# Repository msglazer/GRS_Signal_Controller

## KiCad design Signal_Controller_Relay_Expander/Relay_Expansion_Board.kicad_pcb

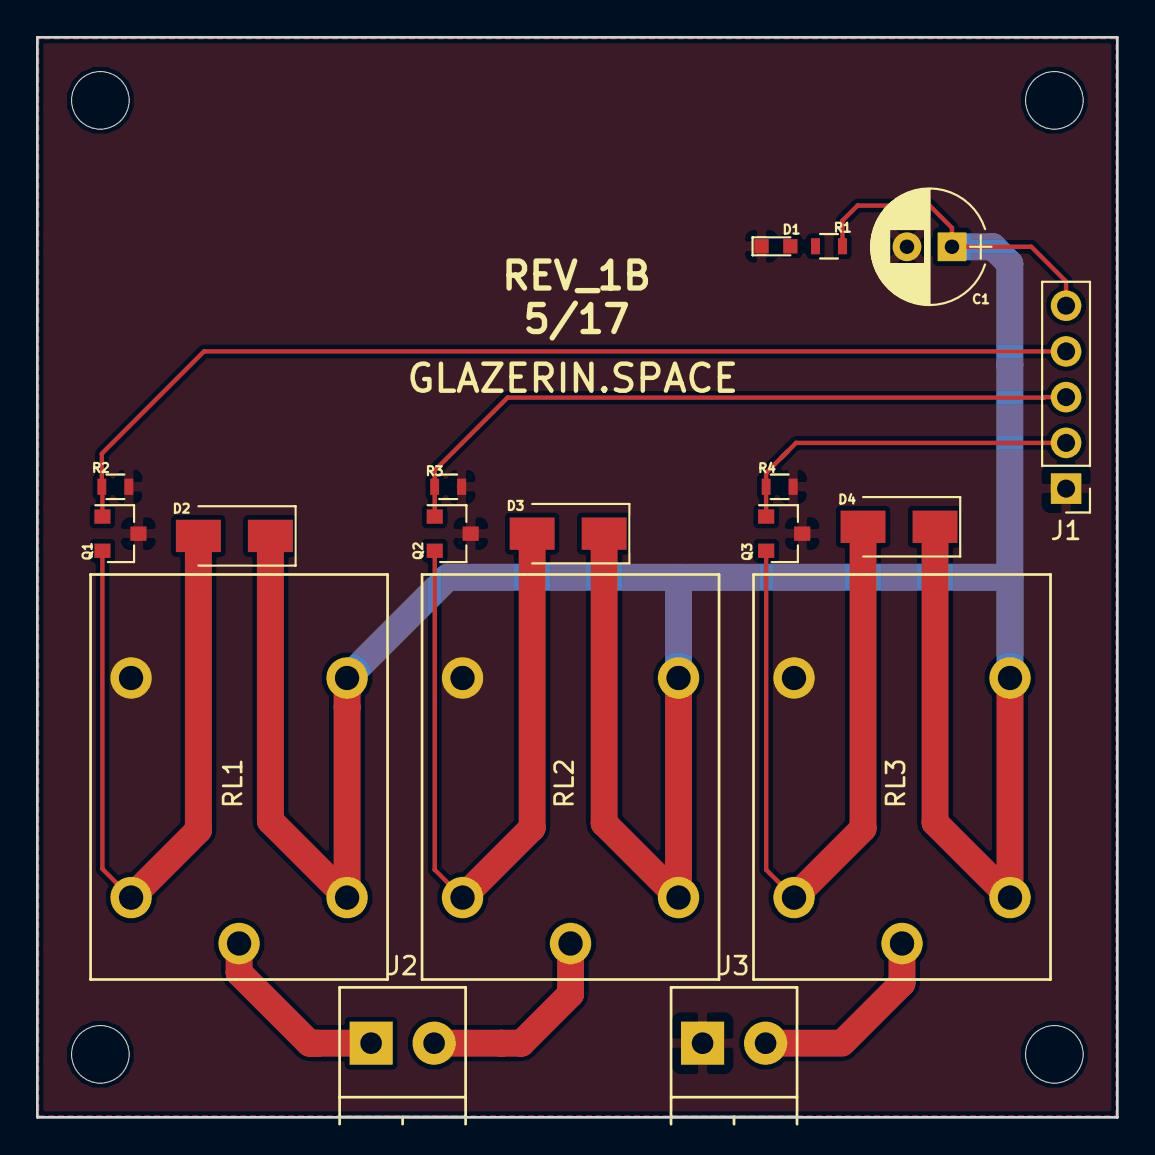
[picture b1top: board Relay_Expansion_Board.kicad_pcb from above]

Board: 2 copper layers, 60.0 x 60.0 mm, 18 parts (0 on the bottom side), 12 nets.

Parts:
C1: 100uF; CP_Radial_D6.3mm_P2.50mm
D1: LED; LED_0603
D2, D3, D4: FM5819-W; D_SMA_Standard
J1: CONN_01X05; Pin_Header_Straight_1x05_Pitch2.54mm
J2, J3: CONN_01X02; TerminalBlock_Pheonix_PT-3.5mm_2pol
Q1, Q2, Q3: 2N7002P,215; SOT-23
R1: R; R_0603
R2, R3, R4: 10K; R_0603
RL1, RL2, RL3: G5LE-1; G5LE-14-DC12

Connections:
+12V: C1.1, D2.1, D3.1, D4.1, J1.5, R1.1, RL1.2, RL1.3, RL2.2, RL2.3, RL3.2, RL3.3
/BULB_2: J3.2, RL3.1
/COIL_2A: J2.1, RL1.1
/COIL_2B: J2.2, RL2.1
/RELAY_4: J1.4, Q1.1, R2.1
/RELAY_5: J1.3, Q2.1, R3.1
/RELAY_6: J1.2, Q3.1, R4.1
GND: C1.2, D1.1, J1.1, J3.1, Q1.3, Q2.3, Q3.3, R2.2, R3.2, R4.2, RL1.4, RL2.4, RL3.4
unnamed: D1.2, R1.2
unnamed: D2.2, Q1.2, RL1.5
unnamed: D3.2, Q2.2, RL2.5
unnamed: D4.2, Q3.2, RL3.5

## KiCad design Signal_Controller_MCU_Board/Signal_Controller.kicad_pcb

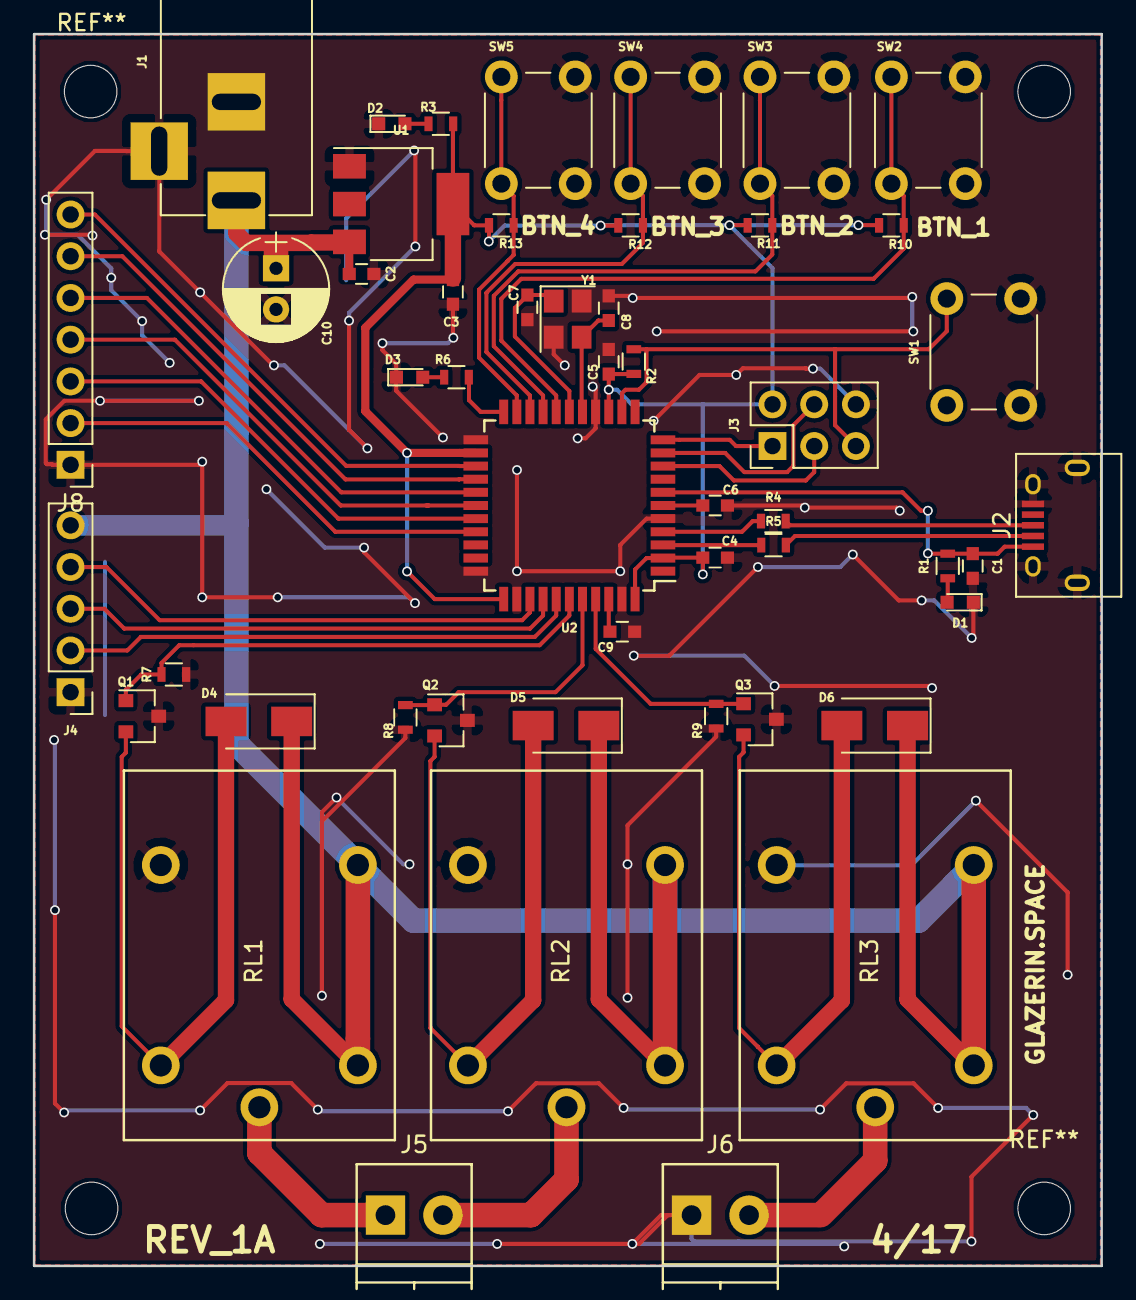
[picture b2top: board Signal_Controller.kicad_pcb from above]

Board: 2 copper layers, 65.0 x 75.0 mm, 50 parts (0 on the bottom side), 42 nets.

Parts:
C1, C2, C3, C4, C5, C6, C9: 1uF; C_0603
C7, C8: 22pF; C_0603
C10: CP1; CP_Radial_D6.3mm_P2.50mm
D1, D2, D3: LED; LED_0603
D4, D5, D6: FM5819-W; D_SMA_Standard
J1: BARREL_JACK
J2: USB_OTG; USB_Micro-B
J3: CONN_02X03; Pin_Header_Straight_2x03_Pitch2.54mm
J4: CONN_01X03; Pin_Header_Straight_1x05_Pitch2.54mm
J5, J6: CONN_01X02; TerminalBlock_Pheonix_PT-3.5mm_2pol
J8: CONN_01X07; Pin_Header_Straight_1x07_Pitch2.54mm
Q1, Q2, Q3: 2N7002P,215; SOT-23
R1, R3, R6: 1K; R_0603
R2, R7, R8, R9, R10, R11, R12, R13: 10K; R_0603
R4, R5: 22; R_0603
RL1, RL2, RL3: G5LE-1; G5LE-14-DC12
SW1, SW2, SW3, SW4, SW5: SW_Push; SW_PUSH_6mm_h13mm
U1: AZ1117IH-5.0TRG1; SOT-223
U2: ATmega32U4; TQFP-44_10x10mm_Pitch0.8mm
Y1: Crystal; Crystal_SMD_3225-4pin_3.2x2.5mm

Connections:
+5V: C3.1, C4.1, C5.1, J3.2, R2.1, R3.1, R10.1, R11.1, R12.1, R13.1, U1.2, U2.2, U2.14, U2.24, U2.34, U2.44
+12V: C2.1, C10.1, D4.1, D5.1, D6.1, J1.1, J4.5, RL1.2, RL1.3, RL2.2, RL2.3, RL3.2, RL3.3, U1.3
/BULB_1: J6.2, RL3.1
/BUTTON_1: R10.2, SW2.1, U2.18
/BUTTON_2: R11.2, SW3.1, U2.19
/BUTTON_3: R12.2, SW4.1, U2.25
/BUTTON_4: R13.2, SW5.1, U2.26
/COIL_1A: J5.1, RL1.1
/COIL_1B: J5.2, RL2.1
/D+: J2.3, R4.2
/D-: J2.2, R5.2
/GPIO_1: J8.5, U2.27
/GPIO_2: J8.4, U2.28
/GPIO_3: J8.3, U2.29
/GPIO_4: J8.2, U2.30
/MISO: J3.1, U2.11
/MOSI: J3.4, U2.10
/RELAY_1: Q1.1, R7.1, U2.39
/RELAY_2: Q2.1, R8.1, U2.40
/RELAY_3: Q3.1, R9.1, U2.41
/RELAY_4: J4.4, U2.36
/RELAY_5: J4.3, U2.37
/RELAY_6: J4.2, U2.38
/RST: J3.5, R2.2, SW1.1, U2.13
/RXI: J8.7, U2.20
/SCK: J3.3, U2.9
/TXO: J8.6, U2.21
/V_BUS: C1.1, J2.1, R1.2, U2.7
GND: C1.2, C2.2, C3.2, C4.2, C5.2, C6.2, C7.1, C8.1, C9.2, C10.2, D1.1, D2.1, D3.1, J1.2, J1.3, J2.5, J2.6, J3.6, J4.1, J6.1, J8.1, Q1.3, Q2.3, Q3.3, R7.2, R8.2, R9.2, RL1.4, RL2.4, RL3.4, SW1.2, SW2.2, SW3.2, SW4.2, SW5.2, U1.1, U2.5, U2.15, U2.23, U2.33, U2.35, U2.43, Y1.2, Y1.4
unnamed: C6.1, U2.6
unnamed: C7.2, U2.17, Y1.1
unnamed: C8.2, U2.16, Y1.3
unnamed: C9.1, U2.42
unnamed: D1.2, R1.1
unnamed: D2.2, R3.2
unnamed: D3.2, R6.1
unnamed: D4.2, Q1.2, RL1.5
unnamed: D5.2, Q2.2, RL2.5
unnamed: D6.2, Q3.2, RL3.5
unnamed: R4.1, U2.4
unnamed: R5.1, U2.3
unnamed: R6.2, U2.22

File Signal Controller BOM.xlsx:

Bill of Materials (BOM) - Wearable Main PCB
> All parts seperated by color, GREEN for Main board, BLUE for Expansion board
Item # | Qty | Ref Des | Manufacturer | Mfg Part # | Dist. Part # | Price Per Unit | Total Price | Description | Package | Type | Datasheet |  |  |  |  |  | Notes
1 | 1 | U1 | Diodes Inc. | AZ1117IH-5.0TRG1 | 621-AZ1117IH-5.0TRG1 | 0.4 | 0.4 | 5V Regulator | SOT-223 | SMD | http://www.mouser.com/ds/2/115/AZ1117-776390.pdf
2 | 1 | U2 | Atmel | ATMEGA32U4RC-AU | 556-ATMEGA32U4RC-AU | 4.09 | 4.09 | Atmega32u4 MCU | TQFP-44 | SMD | http://www.mouser.com/ds/2/268/Atmel-7766-8-bit-AVR-ATmega16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
4 | 7 | C1,C2,C3,C4,C5,C6,C9 | Murata Electronics | GRM188R61E105KA12J | 81-GRM188R61E105KA2J | 0.1 | 0.70000000000000007 | 1uF Capacitor | 0603 | SMD | http://www.mouser.com/ds/2/281/c02e-2905.pdf
5 | 2 | C7,C8 | Vishay / Vitramon | VJ0603A220JXACW1BC | 77-VJ0603A220JXACBC | 0.06 | 0.12 | 22pF Capacitor | 0603 | SMD | http://www.mouser.com/ds/2/427/vjw1bcbascomseries-223529.pdf
7 | 1 | C10 | Lelon | RGA101M1EBK-0611G | 140-RGA101M1EBK0611G | 0.09 | 0.09 | 100uF Capacitor | 6.3mm Radial | Thru Hole | http://www.mouser.com/ds/2/231/144194369515-773075.pdf
8 | 1 | R1,R3,R6 | KOA Speer | RK73H1JTTD1001F | 660-RK73H1JTTD1001F | 0.1 | 0.1 | 1K Ohm Resistor | 0603 | SMD | http://www.mouser.com/ds/2/219/RK73H-5715.pdf
9 | 8 | R2,R7,R8,R9,R10,R11,R12,R13 | KOA Speer | RK73H1JTTD1002F | 660-RK73H1JTTD1002F | 0.1 | 0.8 | 10K Ohm Resistor | 0603 | SMD
11 | 2 | R4,R5 | Bourns | CR0603-FX-22R0ELF | 652-CR0603FX-22R0ELF | 0.1 | 0.2 | 22 Ohm Resistor | 0603 | SMD | http://www.mouser.com/ds/2/54/hpreztr-777398.pdf
13 | 3 | D1,D2,D3 | Kingbright | APT1608SGC | 604-APT1608SGC | 0.14000000000000001 | 0.42000000000000004 | Green LED | 0603 | SMD | http://www.mouser.com/ds/2/216/APT1608SGC-32861.pdf
14 | 3 | D4,D5,D6 | Rectron | FM5819-W | 583-FM5819 | 0.15 | 0.44999999999999996 | Flyback Diode | SMA | SMD | http://www.mouser.com/ds/2/345/fm5817-5819-29163.pdf
15 | 3 | Q1,Q2,Q3 | Nexperia | 2N7002P,215 | 771-2N7002P-215 | 0.14000000000000001 | 0.42000000000000004 | Switching MOSFET | SOT23-3 | SMD | http://www.mouser.com/ds/2/302/2N7002P-838750.pdf
16 | 3 | RL1,RL2,RL3 | Omron Electronics | G5LE-14-DC12 | 653-G5LE-14-DC12 | 1.25 | 3.75 | Power Relay |  | Thru Hole | http://www.mouser.com/ds/2/307/G5LE_0813-267607.pdf
17 | 1 | Y1 | Epson Timing | TSX-3225 16.0000MF09Z-AC3 | 732-TX325-16F09Z-AC3 | 0.51 | 0.51 | Crystal |  | SMD | http://www.mouser.com/ds/2/137/1721499-465440.pdf
18 | 5 | SW1,SW2,SW3,SW4,SW5 | TE Connectivity | 2-1825910-7 | 506-2-1825910-7 | 0.11 | 0.55000000000000004 | Push Button |  | Thru Hole | http://www.mouser.com/ds/2/418/NG_CD_1825910_C9-679022.pdf
19 | 1 | J1 | CUI | PJ-002A | 490-PJ-002A | 0.59 | 0.59 | Barrel Jack |  | Thru Hole | http://www.mouser.com/ds/2/670/pj-037a-516020.pdf
20 | 1 | J2 | Amphenol | 10118194-0001LF | 649-10118194-0001LF | 0.46 | 0.46 | USB Connector |  | SMD | http://www.mouser.com/ds/2/18/10118194AC-944303.pdf
21 | 1 | J3 | TE Connectivity | 4-146262-1 | 571-4-146262-1 | 0.15 | 0.15 | Programming Header |  | Thru Hole
22 | 2 | J5,J6 | Phoenix Contact | 1984617 | 651-1984617 | 0.43 | 0.86 | Terminal Block | 3.5mm | Thru Hole | http://www.mouser.com/ds/2/324/ItemDetail_1984617-920252.pdf
23 | 1 | PCB |  |  |  |  | 0 |  |  | SMD
24 | 1 |  |  |  |  |  | 0 |  |  | SMD
25 | 1 |  |  |  |  |  | 0 |  |  | SMD
1 | 3 | Q1,Q2,Q3 | Nexperia | 2N7002P,215 | 771-2N7002P-215 | 0.14000000000000001 | 0.42000000000000004 | Switching MOSFET | SOT23-3 | SMD | http://www.mouser.com/ds/2/302/2N7002P-838750.pdf
2 | 3 | RL1,RL2,RL3 | Omron Electronics | G5LE-14-DC12 | 653-G5LE-14-DC12 | 1.25 | 3.75 | Power Relay |  | Thru Hole | http://www.mouser.com/ds/2/307/G5LE_0813-267607.pdf
3 | 3 | R1,R2,R3 | KOA Speer | RK73H1JTTD1002F | 660-RK73H1JTTD1002F | 0.1 | 0.30000000000000004 | 10K Ohm Resistor | 0603 | SMD
3 | 1 | R4 | KOA Speer | RK73B1JTTD332J | 660-RK73B1JTTD332J | 0.1 | 0.1 | 3.3K Ohm Resistor | 0603 | SMD | http://www.mouser.com/ds/2/219/RK73B-919.pdf
3 | 1 | C1 | Lelon | RGA101M1EBK-0611G | 140-RGA101M1EBK0611G | 0.09 | 0.09 | 100uF Capacitor | 6.3mm Radial | Thru Hole | http://www.mouser.com/ds/2/231/144194369515-773075.pdf
3 | 3 | D1,D2,D3 | Rectron | FM5819-W | 583-FM5819 | 0.15 | 0.44999999999999996 | Flyback Diode | SMA | SMD | http://www.mouser.com/ds/2/345/fm5817-5819-29163.pdf
3 | 1 | D4 | Kingbright | APT1608SGC | 604-APT1608SGC | 0.14000000000000001 | 0.14000000000000001 | Green LED | 0603 | SMD | http://www.mouser.com/ds/2/216/APT1608SGC-32861.pdf
3 | 1 | PCB |  |  |  |  | 0
3 | 1 | J5,J6 | Phoenix Contact | 1984617 | 651-1984617 | 0.43 | 0.43 | Terminal Block | 3.5mm | Thru Hole | http://www.mouser.com/ds/2/324/ItemDetail_1984617-920252.pdf
3 | 1 |  |  |  |  |  | 0
3 | 1 |  |  |  |  |  | 0
3 | 3 |  |  |  |  |  | 0
 |  |  |  |  | Board Multiplier: | 1 |  | Main board Total:
 |  |  |  |  |  |  |  | 14.66
 |  |  |  |  |  |  |  | Expansion Board Total:
 |  |  |  |  |  |  |  | 5.6799999999999988
 |  |  |  |  |  |  |  | Grand Total:
 |  |  |  |  |  |  |  | 20.34

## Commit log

2017-04-18 :confetti_ball: Added .gitattributes & .gitignore files
2017-04-19 Schematic just about finished
2017-04-19 moved parts to their own repo
2017-04-19 assigning footprints/generating netlist
2017-04-20 PDF output of both schematics
2017-04-20 First revision schematics are completed
    Both board's schematics are done minus some resistor/led values and
    potential pin remapping
2017-04-22 First pass of PCB finished
2017-04-22 added BOM
2017-04-22 Both boards mostly completed
    just need final tweaks, silkscreen stuff etc, all major routing and
    placement done
2017-04-23 Finished BOM
2017-04-23 Added Gerber files
2017-04-23 I looked at it (minor tweaks)
2017-05-08 breaking out a UART instead of just 6 GPIO
2017-05-08 moved relays and connector to line up with controller board
2017-05-09 updated BOM logic
